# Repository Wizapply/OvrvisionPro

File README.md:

# OvrvisionPro
OvrvisionPro SDK - Open Source Project

## Licence
MIT License
Please read "LICENSE" file

# Folders
* 3rdparty : Third party files
* bin : Binaries
* board : PCB borad designs & parts list
* build : Project files for build
* docs : Resource for generating documents
* firmware : OvrvisionPro firmware sources&projects
* include : Public include files
* package
* samples The sample project for the SDK developing.
* src : Sources

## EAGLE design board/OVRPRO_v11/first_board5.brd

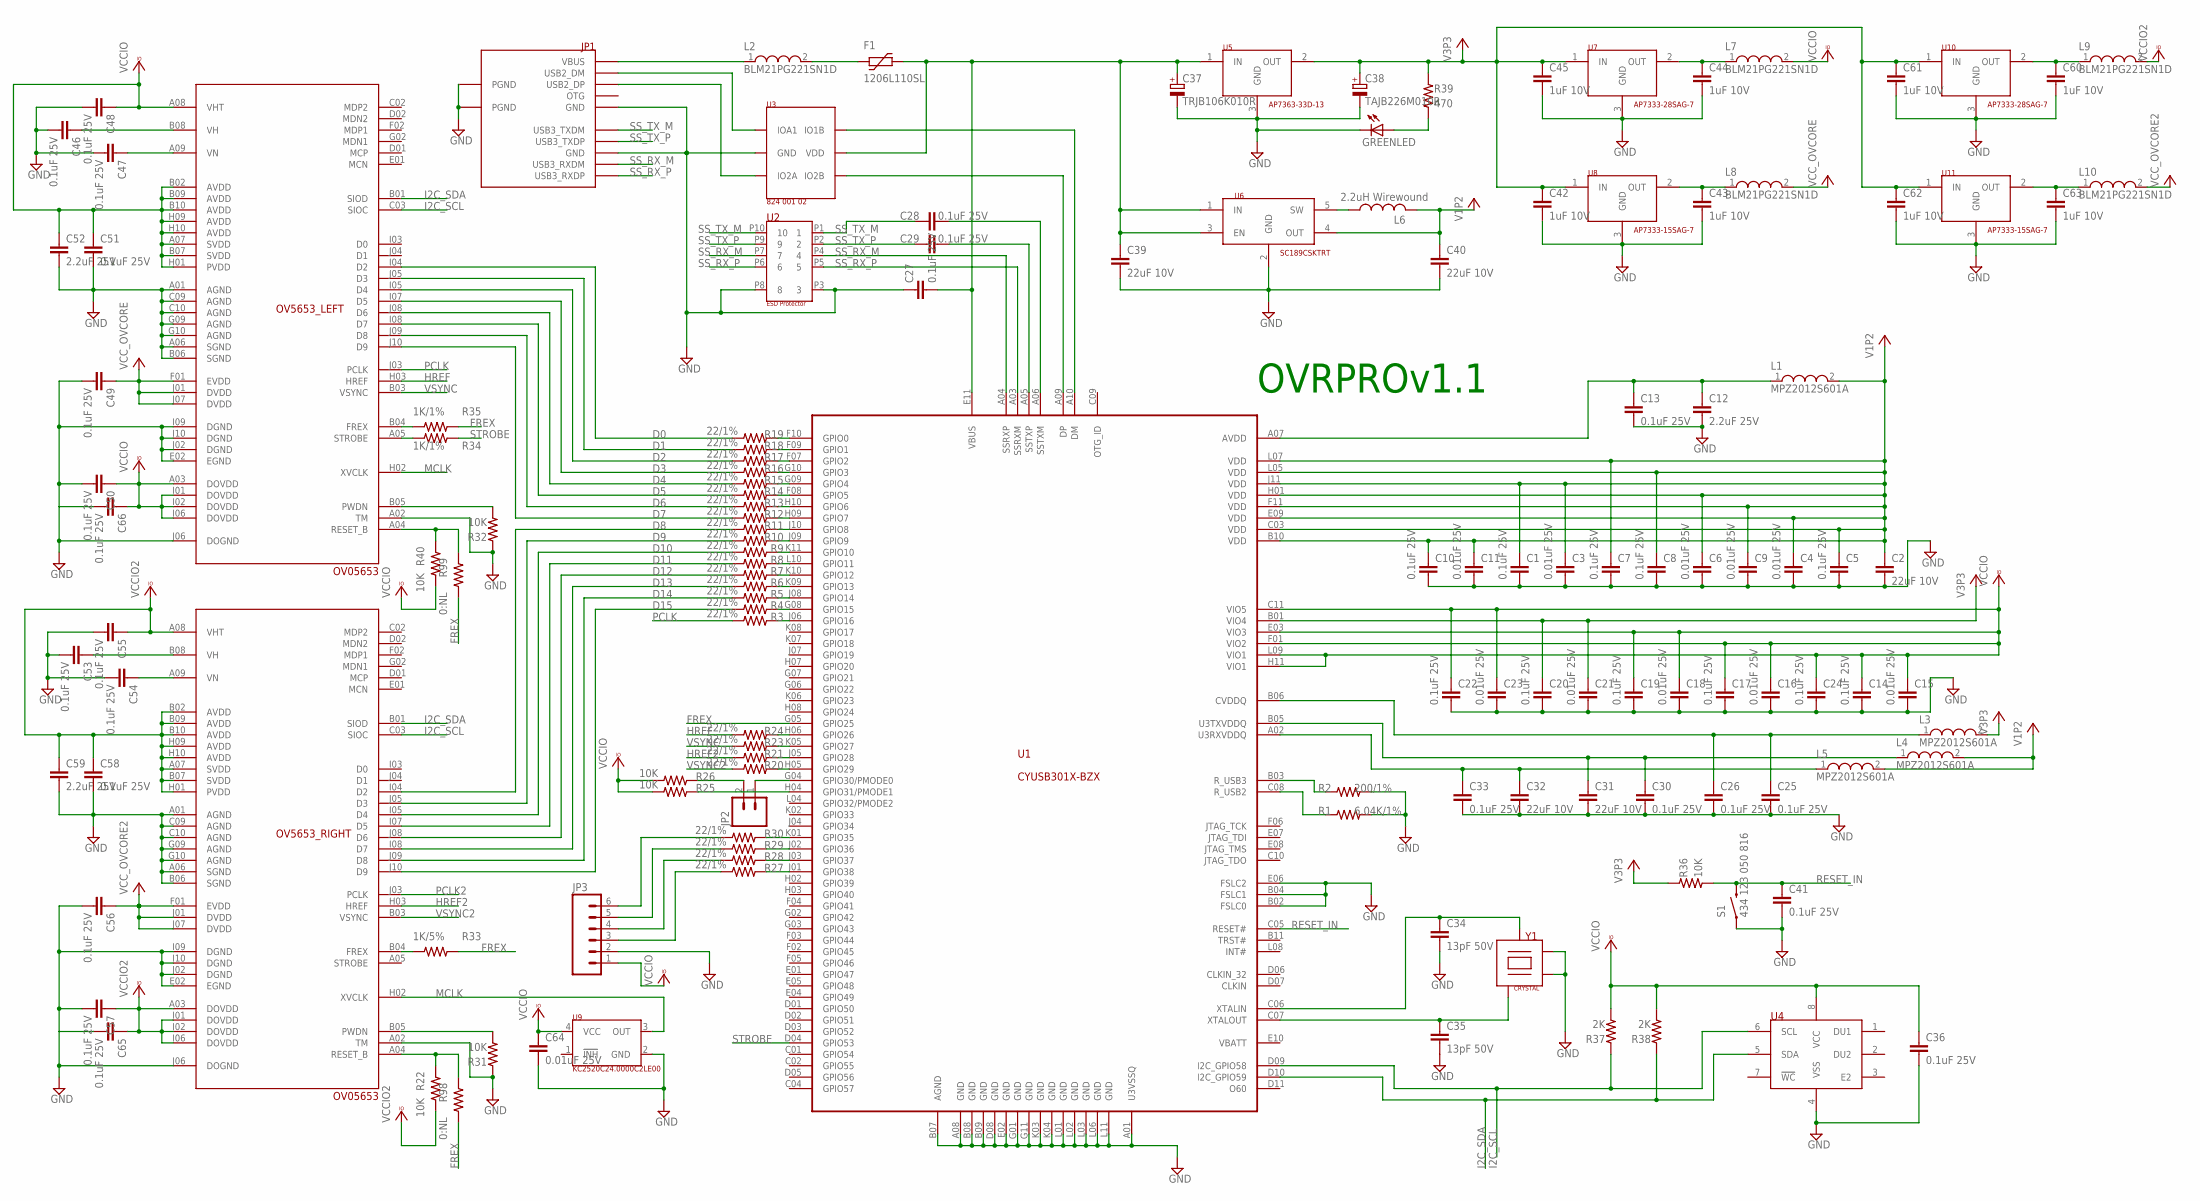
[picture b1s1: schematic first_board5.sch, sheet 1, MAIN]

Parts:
C1, C5, C7, C8, C10, C13, C14, C17, C19, C20, C22, C25, C26, C27, C28, C29, C30, C33, C46, C47, C48, C49, C50, C51, C53, C54, C55, C56, C57, C58, C65, C66: 0.1uF 25V; C0402K
C2, C31, C32, C39, C40: 22uF 10V; C1206
C3, C4, C6, C9, C11, C15, C16, C18, C21, C23, C64: 0.01uF 25V; C0402K
C12, C52, C59: 2.2uF 25V; C0805
C24, C36, C41: 0.1uF 25V; C0402
C34, C35: 13pF 50V; C0402K
C37: TRJB106K010R; CT3528
C38: TAJB226M010R; CT3528
C42, C43, C44, C45, C60, C61, C62, C63: 1uF 10V; C0402
F1: 1206L110SL; 1206L
GREENLED: LED_ESML0603; LED_SML0603
JP1: ZX360D-B-10PUSB3
JP2: M02PTH; 1X02
JP3: M06SILK_FEMALE_PTH; 1X06
L1, L3, L4, L5: MPZ2012S601A; WE-CBA_0805(W=3)
L2, L7, L8, L9, L10: BLM21PG221SN1D; WE-CBA_0805(W=3)
L6: 2.2uH Wirewound; L3225M
OV5653_LEFT, OV5653_RIGHT: OV05653-A66A
R1: 6.04K/1%; SMD1608
R2: 200/1%; SMD1608
R3, R4, R5, R6, R7, R8, R9, R10, R11, R12, R13, R14, R15, R16, R17, R18, R19, R20, R21, R23, R24, R27, R28, R29, R30: 22/1%; SMD1005
R22, R25, R26, R31, R32, R36, R40: 10K; SMD1608
R33: 1K/5%; SMD1005
R34, R35: 1K/1%; SMD1005
R37, R38: 2K; SMD1608
R39: 470; SMD1608
R98, R99: 0:NL; SMD1005
S1: 434 123 050 816; TACTILE-SWITCH-1101NE
U1: CYUSB301X-BZX; BGA121
U2: SP3010-04UTG
U3: WE-82400102
U4: M24M02-DRMN6TP; SO-08
U5: AP7363-33D-13; TO-252
U6: SC189CSKTRT; SOT23-5
U7, U10: AP7333-28SAG-7; SOT23
U8, U11: AP7333-15SAG-7; SOT23
U9: KC2520C24.0000C2LE00; KC2520C-C2
Y1: NX2520SACRY

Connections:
312: R15.2, U1.G09 (GPIO4)
321: R16.2, U1.G10 (GPIO3)
+3V3: C20.1, C21.1, C38.+, C42.1, C45.1, C61.1, C62.1, L3.2, R36.1, R39.1, U1.B01 (VIO4), U5.2 (OUT), U7.1 (IN), U8.1 (IN), U10.1 (IN), U11.1 (IN)
+5V: C1.1, C2.1, C3.1, C4.1, C5.1, C6.1, C7.1, C8.1, C9.1, C10.1, C11.1, C40.1, L1.2, L4.2, L5.2, L6.2, U1.B10 (VDD), U1.C03 (VDD), U1.E09 (VDD), U1.F11 (VDD), U1.H01 (VDD), U1.J11 (VDD), U1.L05 (VDD), U1.L07 (VDD), U6.4 (OUT)
D0: OV5653_LEFT.I04 (D2), R19.1
D1: OV5653_LEFT.J05 (D3), R18.1
D2: OV5653_LEFT.I05 (D4), R17.1
D3: OV5653_LEFT.I07 (D5), R16.1
D4: OV5653_LEFT.J08 (D6), R15.1
D5: OV5653_LEFT.I08 (D7), R14.1
D6: OV5653_LEFT.J09 (D8), R13.1
D7: OV5653_LEFT.J10 (D9), R12.1
D8: OV5653_RIGHT.I04 (D2), R11.1
D9: OV5653_RIGHT.J05 (D3), R10.1
D10: OV5653_RIGHT.I05 (D4), R9.1
D11: OV5653_RIGHT.I07 (D5), R8.1
D12: OV5653_RIGHT.J08 (D6), R7.1
D13: OV5653_RIGHT.I08 (D7), R6.1
D14: OV5653_RIGHT.J09 (D8), R5.1
D15: OV5653_RIGHT.J10 (D9), R4.1
FREX: R33.2, R35.2, R98.1, R99.1, U1.G05 (GPIO25)
GND: C1.2, C2.2, C3.2, C4.2, C5.2, C6.2, C7.2, C8.2, C9.2, C10.2, C11.2, C12.2, C13.2, C14.2, C15.2, C16.2, C17.2, C18.2, C19.2, C20.2, C21.2, C22.2, C23.2, C24.2, C25.2, C26.2, C27.1, C30.2, C31.2, C32.2, C33.2, C34.2, C35.2, C36.2, C37.-, C38.-, C39.2, C40.2, C41.2, C42.2, C43.2, C44.2, C45.2, C46.2, C47.2, C48.2, C49.2, C50.2, C51.2, C52.2, C53.2, C54.2, C55.2, C56.2, C57.2, C58.2, C59.2, C60.2, C61.2, C62.2, C63.2, C64.2, C65.2, C66.2, GREENLED.C, JP1.GND@1 (GND), JP1.GND@2 (GND), JP1.PGND@1 (PGND), JP1.PGND@2 (PGND), JP3.2, OV5653_LEFT.A01 (AGND), OV5653_LEFT.A02 (TM), OV5653_LEFT.A06 (SGND), OV5653_LEFT.B06 (SGND), OV5653_LEFT.C09 (AGND), OV5653_LEFT.C10 (AGND), OV5653_LEFT.E02 (EGND), OV5653_LEFT.G09 (AGND), OV5653_LEFT.G10 (AGND), OV5653_LEFT.I09 (DGND), OV5653_LEFT.I10 (DGND), OV5653_LEFT.J02 (DGND), OV5653_LEFT.J06 (DOGND), OV5653_RIGHT.A01 (AGND), OV5653_RIGHT.A02 (TM), OV5653_RIGHT.A06 (SGND), OV5653_RIGHT.B06 (SGND), OV5653_RIGHT.C09 (AGND), OV5653_RIGHT.C10 (AGND), OV5653_RIGHT.E02 (EGND), OV5653_RIGHT.G09 (AGND), OV5653_RIGHT.G10 (AGND), OV5653_RIGHT.I09 (DGND), OV5653_RIGHT.I10 (DGND), OV5653_RIGHT.J02 (DGND), OV5653_RIGHT.J06 (DOGND), R1.2, R2.2, R31.1, R32.1, S1.1, U1.A01 (U3VSSQ), U1.A08 (GND), U1.B02 (FSLC0), U1.B04 (FSLC1), U1.B07 (AGND), U1.B08 (GND), U1.B09 (GND), U1.D08 (GND), U1.E02 (GND), U1.E06 (FSLC2), U1.G01 (GND), U1.G11 (GND), U1.K03 (GND), U1.K04 (GND), U1.L01 (GND), U1.L02 (GND), U1.L03 (GND), U1.L06 (GND), U1.L11 (GND), U2.P3 (3), U2.P8 (8), U3.P2 (GND), U4.4 (VSS), U5.3 (GND), U6.2 (GND), U7.3 (GND), U8.3 (GND), U9.2 (GND), U10.3 (GND), U11.3 (GND), Y1.P2, Y1.P4
HREF: OV5653_LEFT.H03 (HREF), R24.1
HREF2: OV5653_RIGHT.H03 (HREF), R21.1
I2C_SCL: OV5653_LEFT.C03 (SIOC), OV5653_RIGHT.C03 (SIOC), R37.1, U1.D09 (I2C_GPIO58), U4.6 (SCL)
I2C_SDA: OV5653_LEFT.B01 (SIOD), OV5653_RIGHT.B01 (SIOD), R38.1, U1.D10 (I2C_GPIO59), U4.5 (SDA)
MCLK: OV5653_LEFT.H02 (XVCLK), OV5653_RIGHT.H02 (XVCLK), U9.3 (OUT)
unnamed: R2.1, U1.B03 (R_USB3)
unnamed: C12.1, C13.1, L1.1, U1.A07 (AVDD)
unnamed: R1.1, U1.C08 (R_USB2)
unnamed: JP2.2, R26.2
unnamed: R25.2, U1.H04 (GPIO31/PMODE1)
unnamed: C25.1, C26.1, L3.1, U1.B06 (CVDDQ)
unnamed: L6.1, U6.5 (SW)
unnamed: F1.P$1 (1), L2.2
unnamed: C44.1, L7.1, U7.2 (OUT)
unnamed: JP1.USB2_DM, U3.P1 (IOA1)
unnamed: JP1.USB2_DP, U3.P3 (IO2A)
unnamed: C32.1, C33.1, L5.1, U1.A02 (U3RXVDDQ)
unnamed: U1.A10 (DM), U3.P6 (IO1B)
unnamed: U1.A09 (DP), U3.P4 (IO2B)
unnamed: C30.1, C31.1, L4.1, U1.B05 (U3TXVDDQ)
unnamed: C34.1, U1.C06 (XTALIN), Y1.P1
unnamed: C35.1, U1.C07 (XTALOUT), Y1.P3
unnamed: GREENLED.A, R39.2
unnamed: C47.1, OV5653_LEFT.A09 (VN)
unnamed: C46.1, OV5653_LEFT.B08 (VH)
unnamed: C28.2, U1.A06 (SSTXM)
unnamed: C29.2, U1.A05 (SSTXP)
unnamed: OV5653_RIGHT.B05 (PWDN), R31.2
unnamed: JP3.6, R30.1
unnamed: OV5653_LEFT.B05 (PWDN), R32.2
unnamed: JP3.5, R29.1
unnamed: JP3.4, R28.1
unnamed: JP3.3, R27.1
unnamed: R30.2, U1.K01 (GPIO35)
unnamed: R29.2, U1.J02 (GPIO36)
unnamed: R28.2, U1.J03 (GPIO37)
unnamed: R27.2, U1.J01 (GPIO38)
unnamed: C27.2, C37.+, C39.1, F1.P$2 (2), U1.E11 (VBUS), U3.P5 (VDD), U5.1 (IN), U6.1 (IN), U6.3 (EN)
unnamed: JP1.VBUS, L2.1
unnamed: C43.1, L8.1, U8.2 (OUT)
unnamed: C60.1, L9.1, U10.2 (OUT)
unnamed: C63.1, L10.1, U11.2 (OUT)
unnamed: JP2.1, U1.G04 (GPIO30/PMODE0)
unnamed: OV5653_RIGHT.B04 (FREX), R33.1
unnamed: OV5653_LEFT.A05 (STROBE), R34.1
unnamed: R3.2, U1.J06 (GPIO16)
unnamed: R11.2, U1.J10 (GPIO8)
unnamed: R10.2, U1.J09 (GPIO9)
unnamed: R9.2, U1.K11 (GPIO10)
unnamed: R8.2, U1.L10 (GPIO11)
unnamed: R7.2, U1.K10 (GPIO12)
unnamed: R6.2, U1.K09 (GPIO13)
unnamed: R5.2, U1.J08 (GPIO14)
unnamed: R4.2, U1.G08 (GPIO15)
unnamed: R21.2, U1.J05 (GPIO28)
unnamed: R20.2, U1.H05 (GPIO29)
unnamed: OV5653_LEFT.B04 (FREX), R35.1
unnamed: R24.2, U1.H06 (GPIO26)
unnamed: R23.2, U1.K05 (GPIO27)
unnamed: R14.2, U1.F08 (GPIO5)
unnamed: R13.2, U1.H10 (GPIO6)
unnamed: R12.2, U1.H09 (GPIO7)
unnamed: R17.2, U1.F07 (GPIO2)
unnamed: R18.2, U1.F09 (GPIO1)
unnamed: R19.2, U1.F10 (GPIO0)
OV_RESET1: OV5653_LEFT.A04 (RESET_B), R40.2, R99.2
OV_RESET2: OV5653_RIGHT.A04 (RESET_B), R22.2, R98.2
PCLK: OV5653_LEFT.J03 (PCLK), R3.1
PCLK2: OV5653_RIGHT.J03 (PCLK)
RESET_IN: C41.1, R36.2, S1.2, U1.C05 (RESET#)
SS_RX_M: JP1.USB3_RXDM, U1.A04 (SSRXP), U2.P4 (4), U2.P7 (7)
SS_RX_P: JP1.USB3_RXDP, U1.A03 (SSRXM), U2.P5 (5), U2.P6 (6)
SS_TX_M: C28.1, JP1.USB3_TXDM, U2.P1 (1), U2.P10 (10)
SS_TX_P: C29.1, JP1.USB3_TXDP, U2.P2 (2), U2.P9 (9)
STROBE: R34.2, U1.D04 (GPIO53)
VCC: C49.1, L8.2, OV5653_LEFT.F01 (EVDD), OV5653_LEFT.J01 (DVDD), OV5653_LEFT.J07 (DVDD)
VCC2: C56.1, L10.2, OV5653_RIGHT.F01 (EVDD), OV5653_RIGHT.J01 (DVDD), OV5653_RIGHT.J07 (DVDD)
VCCIO: C14.1, C15.1, C16.1, C17.1, C18.1, C19.1, C22.1, C23.1, C24.1, C36.1, C48.1, C50.1, C51.1, C52.1, C55.1, C57.1, C58.1, C59.1, C64.1, C65.1, C66.1, JP3.1, L7.2, L9.2, OV5653_LEFT.A03 (DOVDD), OV5653_LEFT.A07 (SVDD), OV5653_LEFT.A08 (VHT), OV5653_LEFT.B02 (AVDD), OV5653_LEFT.B07 (SVDD), OV5653_LEFT.B09 (AVDD), OV5653_LEFT.B10 (AVDD), OV5653_LEFT.H01 (PVDD), OV5653_LEFT.H09 (AVDD), OV5653_LEFT.H10 (AVDD), OV5653_LEFT.I01 (DOVDD), OV5653_LEFT.I02 (DOVDD), OV5653_LEFT.I06 (DOVDD), OV5653_RIGHT.A03 (DOVDD), OV5653_RIGHT.A07 (SVDD), OV5653_RIGHT.A08 (VHT), OV5653_RIGHT.B02 (AVDD), OV5653_RIGHT.B07 (SVDD), OV5653_RIGHT.B09 (AVDD), OV5653_RIGHT.B10 (AVDD), OV5653_RIGHT.H01 (PVDD), OV5653_RIGHT.H09 (AVDD), OV5653_RIGHT.H10 (AVDD), OV5653_RIGHT.I01 (DOVDD), OV5653_RIGHT.I02 (DOVDD), OV5653_RIGHT.I06 (DOVDD), R22.1, R25.1, R26.1, R37.2, R38.2, R40.1, U1.C11 (VIO5), U1.E03 (VIO3), U1.F01 (VIO2), U1.H11 (VIO1), U1.L09 (VIO1), U4.8 (VCC), U9.4 (VCC)
VH: C53.1, OV5653_RIGHT.B08 (VH)
VN: C54.1, OV5653_RIGHT.A09 (VN)
VSYNC: OV5653_LEFT.B03 (VSYNC), R23.1
VSYNC2: OV5653_RIGHT.B03 (VSYNC), R20.1

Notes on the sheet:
OVRPROv1.1

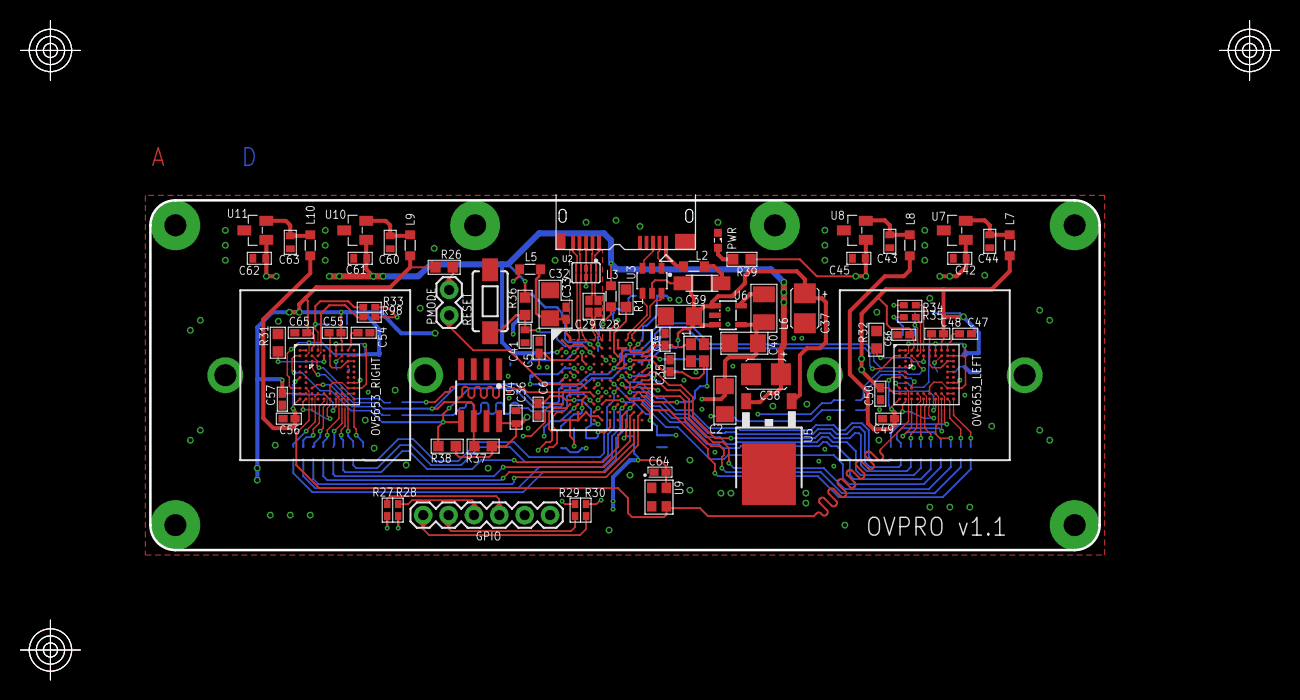
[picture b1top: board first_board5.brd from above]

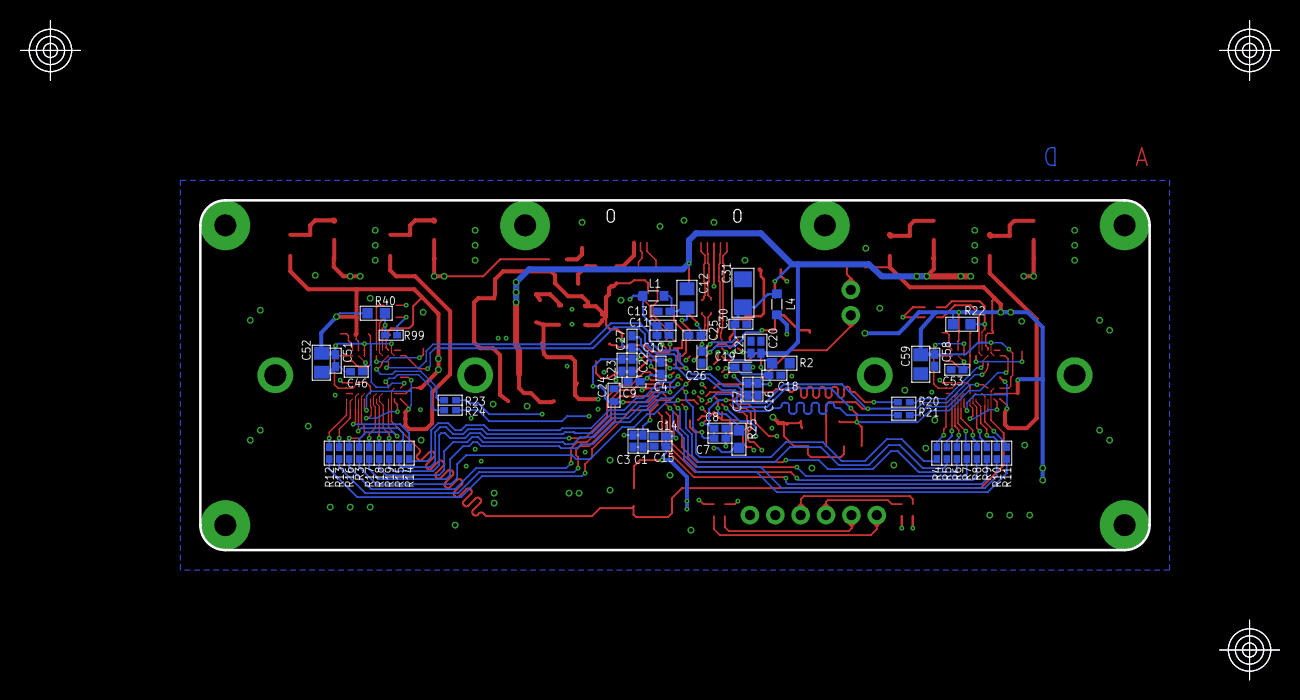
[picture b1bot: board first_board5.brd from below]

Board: 4 copper layers, 95.0 x 35.0 mm, 138 parts (60 on the bottom side), 103 nets.

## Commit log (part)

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2015-11-17 ヘッダファイルに埋め込んだカーネルからプログラムを生成
2015-11-17 add libraries
2015-11-18 ・ファームウェアを更新しました（EEPROMにセーブする機能） ・SDKにセーブ機能 ・C#プログラムにカメラ設定をリアルタイムに変更できるダイアログを追加 ・細かい関数の修正
2015-11-18 ・binフォルダ追加
2015-11-18 Modify create kernel
2015-11-18 RAWデータ（uchar）でデータを返すAPIも追加、Matを使いたくない場合はこちらも使用できます
2015-11-19 ・OvrvisionSDK for Unityを追加（AR部分は未実装） ・GetImageを一部変更
2015-11-19 samplesフォルダにサンプルコードを追加
2015-11-19 sampleのファイルを一部移動および削除
2015-11-19 サンプルプログラムにビルド後イベントを追加
2015-11-20 ・プロジェクトOpenCVの不具合を修正 ・OculusSDKv0.8をコミット ・oculus用のアプリケーションのプロジェクトを追加 ・::CoInitialize(NULL)関連の不具合を修正 ・UnityのARを追加（一部修正中）
2015-11-20 ・不具合を修正
2015-11-20 ・ovrvisionアプリケーションにOculusSDKのモノを追加
2015-11-21 OpenGL_windowsプロジェクトを追加
2015-11-21 sampleにモード切替追加。
2015-11-22 OpenGLサンプルプロジェクト追加
2015-11-22 フレームバッファをインスタンス生成で行う。 また、OpenGL/D3D連携のためのCPUへの転送を行わないAPIを追加
2015-11-23 OpenGL連携のテクスチャーAPI追加
2015-11-24 ・Ovrvision AR関連を追加しました。 ・Unityプログライン更新 ・キャリブレーションソフトウェアの不具合を修正しました。
2015-11-24 Direct3D連携の機能拡張チェック組み込み
2015-11-24 縮小グレースケール画像、スキンカラー抽出などのAPIを追加（未完成）
2015-11-25 GPUの拡張機能情報取得関数を追加。
2015-11-25 sample/OpenCVに画像保存を追加
2015-11-26 連携テクスチャー生成APIを追加
2015-11-26 手の色域調査
2015-11-27 ・トラッキング用のクラスを追加 ・Unity5プラグイン完成
2015-11-27 ・ARエンジン「Metaio」のプログラムを追加 ・OvrvisionProで起動が停止する不具合を修正 ・ファームウェアを更新
2015-11-27 ・アップロードできなかったので削除
2015-11-27 ・容量リミットのため削除
2015-11-27 画像取得時にクロップする関数を追加
2015-11-28 ・不具合の修正
2015-11-28 remove 1 project
2015-11-28 ・OvrvisionARを修正 ・Doxygen形式のコメントを追加
2015-11-28 色空間の検討
2015-11-29 片手の抽出。色相と彩度をハードコーディング
2015-11-30 両手の肌色抽出
2015-11-30 First Release
2015-11-30 ヒストグラム作成
2015-11-30 ガウシアンブラーで、疑似ピークをつぶす。照明の加減で色相が飛ぶことがあるが、これは今回は無視する
2015-12-01 ・ファームウェアを更新しました。
2015-12-01 ・公開するSDK修正
2015-12-01 複数GPUの場合、コア数と周波数の乗数が最も大きいものを選択する
2015-12-02 ・Version 1.01
2015-12-02 個々の画像から残存ノイズをerodeで削減。
2015-12-02 HSV色空間でmedianBlurをかけてノイズ除去後に色域抽出
2015-12-02 複数GPUの検出情報
2015-12-02 エピポーラ情報を読む
2015-12-02 左右のカメラのエピポーラ処理
2015-12-03 視差情報のテスト
2015-12-03 大きい域のみ考慮する
2015-12-03 ・簡易トラッキングを実装 ・Unity5での不具合を修正 ・一部カメラ起動が出来ない不具合を修正
2015-12-04 ・キャリブレーションツールの不具合を修正
2015-12-04 平行化修正案
2015-12-04 ステレオ平行化ほぼ修正
2015-12-04 ステレオ平行化修正版
2015-12-04 OpenCL関数の追加
2015-12-04 OpenCL動作テスト
2015-12-04 縮小の動作を確認
2015-12-05 HSV変換テスト
2015-12-05 縮小グレースケール関数を追加
2015-12-05 Remap修正しました
2015-12-05 色域判定関数を追加
2015-12-05 HSV変換の前にガウシアンブラーをかけた
2015-12-05 肌色領域マスク生成までOpenCLに実装
2015-12-06 追加gaussian blur
2015-12-06 ・Unityでの不具合を修正 ・高性能PCを動作させるとOvrvisionが停止する不具合を修正
2015-12-06 HSV色変換のバグ修正
2015-12-06 メディアンフィルターを実装、ガウシアンと比較評価中
2015-12-07 ・メモリリークの個所を確認 ・不具合を修正
2015-12-07 ・ドキュメントを更新
2015-12-07 リークテスト
2015-12-07 メモリリーク修正
2015-12-07 メディアンフィルターに5x5を追加して比較検討
2015-12-07 fix kernel
2015-12-08 ・一部メモリリークを修正
2015-12-08 肌色抽出用のカーネルを二種追加
2015-12-08 Close関数を追加。
2015-12-08 OpenGL連携テスト用のFreeGlutを追加
2015-12-09 ・カメラモードの切り替えを可能にしました。
2015-12-09 OpenGLテクスチャー連携テスト中
2015-12-09 OpenGL連携テストのためのコールバック関数追加
2015-12-09 コールバックプラットフォーム依存部分を切り分け
2015-12-09 GPUがOpenCL 1.2未満の場合、例外を投げて起動できないようにしました
2015-12-10 ・Version1.2
2015-12-10 ・OvrvisionProのカバーデザインをアップ
2015-12-10 肌色処理でOpenMPの効果を検討
2015-12-10 OpenMPで肌色領域テスト
2015-12-10 縮小画像の扱いを中断
2015-12-10 OpenMP化検討
2015-12-10 縮小画像を保持する準備
2015-12-10 縮小画像を残す
2015-12-10 暫定版の肌色抽出関数追加。まだ残存ノイズ多い
2015-12-10 合成カーネルの修正
2015-12-11 ・Unityのエラーを修正 ・CSharpのエラーを修正
2015-12-11 Remapかからないバグを修正
2015-12-11 肌色抽出処理のカーネルを修正
2015-12-11 肌色抽出でのGPU側リリースを修正
2015-12-11 Radeon 対応
2015-12-11 ・LensのDatasheepを追加 ・ドキュメントを更新
2015-12-12 ・ソースコードのエンコードをUTF-8Nに変更
2015-12-12 コメントなどを修正。機能的には変更なし
2015-12-12 ・Mac対応
2015-12-12 ・Mac用の画像USBストリームプログラムコードを追加
2015-12-12 MacOSに対応しました。 OpenCLの部分も一部変更しました。
2015-12-12 コード分析で指摘された部分の修正
2015-12-12 cl_eventの開放。
2015-12-12 OpenCLの開放漏れを修正
2015-12-12 肌色抽出の評価関数の閾値設定を追加
2015-12-13 凸包と凹状欠損で、手を絞り込む
2015-12-13 二段階で凸包の絞り込み。
2015-12-14 ・ホワイトバランス設定を修正
2015-12-14 ・ドキュメントの更新 ・ホワイトバランスオートの不具合を修正
2015-12-14 左右の画像の凸包をマッチング
2015-12-14 kalman filterによる抽出オブジェクトの追跡テスト
2015-12-14 肌色抽出の評価関数シミュレーション
2015-12-14 HSV変換のカーネル修正
2015-12-15 手の検出シミュレーション
2015-12-15 シミュレーションで100フレーム程度ヒストグラムをとって色範囲を特定。
2015-12-16 手の検出関数を追加、ただしまだ色範囲の推定が調整中で手が虫食い状態になる
2015-12-16 キャリブレーション結果を表示する
2015-12-16 手の抽出の縮小設定を追加
2015-12-16 五指の検出テスト（S）
2015-12-16 肌色推定を改良
2015-12-17 Charpの不具合を修正
2015-12-17 ・MacOSの開発
2015-12-17 ・MacOS開発
2015-12-17 check contour areas
2015-12-17 GPUとのテクスチャーシェアリングに伴う関数を追加。実装中
2015-12-17 GPUテクスチャーを実装、テスト中
2015-12-17 Sharing texture with OpenGL/D3D11
2015-12-18 ・MacOS
2015-12-18 MacOS開発と不具合調査
2015-12-19 GPUテクスチャー生成関数を追加。
2015-12-19 GPUテクスチャー関連関数の追加修正
2015-12-19 テクスチャー関係の整理
2015-12-19 GPUテクスチャーマージ
2015-12-19 テクスチャー関係関数を整理中
2015-12-19 MACOSXのスイッチも追加しましたが、問題あるかも
2015-12-20 MAXOSXでのOpenGL共有テクスチャーのコードが古かったので、一旦コメントアウト
2015-12-20 GPU共有テクスチャー修正
2015-12-20 MACOSX対応
2015-12-20 Xcode7では、これまで使用していたOpenCL/OpenGL共有テクスチャーの関数が使えなくなっているため、一旦ペンディング
2015-12-20 GPU共有テクスチャーの生成、更新関数を修正
2015-12-20 MACOSX対応の修正
2015-12-20 D3D11テスト用にDirectXTexライブラリを追加
2015-12-20 デバッグのため、GPU内の処理途中の画像を取得。テクスチャーが表示されない
2015-12-21 ・MACOSのコントロール
2015-12-21 ・ファームウェアテスト
2015-12-21 OpenGLの環境テスト中
2015-12-21 OpenCL1.2関数に絞って修正
2015-12-21 初期化バグ修正
2015-12-21 NVIDIA用のヘッダファイルを追加
2015-12-21 GPUテクスチャーのデータ取得
2015-12-21 OpenGLを指定した場合の異常系対処
2015-12-21 MACOSXではOpenGL連携関数が使えない？ので修正
2015-12-22 ・oculus sdk修正
2015-12-22 ・MACOSの
2015-12-22 ・MACOS キャリブレーションアプリ開発
2015-12-22 CheckGPUでOvrvisionPro適格性の判定を返す（メモリ容量については調査中）
2015-12-22 OpenCLバージョンも表示するよう追加
2015-12-22 暫定的にメモリ容量を判定
2015-12-23 ・ファームウェアでの検証と変更
2015-12-23 D3D11でのGPUテクスチャー動作テスト
2015-12-23 D3D11修正
2015-12-23 MACOSXではOpenGLの一部関数が有効になっていないため外す
2015-12-23 D3D11のGPU共有テクスチャー使用法をコメントに追加
2015-12-23 ヘッダファイルにGPU共有テクスチャーの使用法を追記
2015-12-24 ・ファーム調査
2015-12-24 コメント修正。機能的には変更なし
2015-12-24 MACOS
2015-12-24 ・Version1.4
2015-12-24 肌色抽出用カーネル追加
2015-12-24 肌色推定時のメッセージを変更
2015-12-25 肌色推定の精度改良にトーン補正用カーネル追加、
2015-12-26 諧調補正マップ追加
2015-12-26 縮小時の階調補正カーネル追加
2015-12-26 縮小時に階調補正かけて肌色推定の観察
2015-12-26 諧調補正マップ修正
2015-12-26 無駄コード削除
2015-12-27 肌色抽出のバグ修正
2015-12-27 OpenCLのイベントチェーンを修正
2015-12-27 Debugビルドができるように修正
2015-12-27 OpenGLテクスチャーのバグ修正
2015-12-28 ・制御部分修正
2015-12-28 OpenCLのイベントチェーン修正
2015-12-28 GPU共有テクスチャーのコメント追加
2015-12-28 MACOS v1.3
2015-12-28 OpenCLイベントチェーンを改良
2015-12-28 階調補正カーネルを追加
2015-12-29 ・Version 1.3
2015-12-29 Version 1.3 publish
2015-12-29 Version 1.3b mac publish
2015-12-30 ・ファームウェア変更
2015-12-30 OpenGLサンプルに肌色推定を組み込み
2015-12-31 テクスチャーの上下修正
2016-01-04 動作テスト用のプロジェクト修正
2016-01-04 動作テスト用OpenGLプロジェクト
2016-01-04 OpenGLプロジェクト修正
2016-01-05 レイテンシ測定。
2016-01-05 階調補正による肌色推定の精度改良
2016-01-05 GPU共有テクスチャーのレイテンシ測定
2016-01-06 ・ファームウェア改良 ・ハンドトラッキング改良
2016-01-07 D3D11のGPU共有テクスチャー修正
2016-01-07 MACOSX版にGPU共有テクスチャー組み込み
2016-01-07 MACOSX版とWindows版をマージ
2016-01-07 MACOSXコードをLinuxと分離
2016-01-07 MACOSXテクスチャー修正
2016-01-07 MACOSX版修正
2016-01-07 MACOSXでのGPU検出修正
2016-01-07 D3D11のGPU共有テクスチャーテストに肌色推定を追加
2016-01-08 ・Version 1.31
2016-01-08 ・バグ修正
2016-01-09 ・USB3.0の転送が停止する不具合を修正 ・USB3.0転送パフォーマンスを向上
2016-01-09 左右で異なるフィルター処理していたのを修正
2016-01-09 OpenCVプロジェクト外しました
2016-01-11 ・ovrvision_appの画像サイズを修正
2016-01-12 OpenCLのイベントチェーン強化
2016-01-12 肌色推定時のバグ修正
2016-01-12 Add TODO comment into UpdateImageTextures
2016-01-14 Version 1.32
2016-01-14 Version 1.32 firmware
2016-01-14 UpdateImageTexturesを修正、縮小画像もOpenGL共有テクスチャーとして使用できます
2016-01-14 OpenGLサンプルプロジェクト修正
2016-01-16 ・Version 1.4
2016-01-16 MAC Version 1.4
2016-01-21 Modify for linux edition
2016-01-22 Prepare for Linux edition
2016-01-22 Prototype of Linux edition
2016-01-22 カメラ制御以外をLinux用に修正。カメラ部分は未実装
2016-01-22 Linux edition UNDER CONDTRUCTION
2016-01-23 Video4Linuxのフォーマット指定を変更
2016-01-23 Fix V4l functions
2016-01-23 Add QueryCapability to Video4Linux
2016-01-25 Add Video4Linux query program
2016-01-28 V4Lの接続テスト
2016-01-28 ・Unityの使いやすさ向上
2016-01-28 V4Lカメラ情報取得
2016-01-28 Modify V4L
2016-01-28 Search 'OvrvisionPro' device
2016-01-29 ・UnityのOpenGL不具合修正
2016-01-29 Modify MMAP mode on V4L
2016-01-29 Set resolution on V4L
2016-01-30 V4L capture test
2016-02-01 ・プロジェクト移動 ・ARのシステムを最適化 ・ファームウェア修正
2016-02-02 Version 1.5
2016-02-02 ・Version 1.5 docs
2016-02-03 Fix crop image on V4L2
2016-02-04 ・FirmGPIOテスト ・UnityでDirectX12を実装、開発中
2016-02-05 V4L camera control NOT YET IMPLEMENTED
2016-02-06 ・RAW描画を追加
2016-02-06 mac os
2016-02-06 ・registerを削除 ・
2016-02-06 Add crop to V4L2
2016-02-08 Linux対応(途中)
2016-02-09 ・Ｌｉｎｕｘ対応（開発中）
2016-02-09 ・Linux対応(開発中)
2016-02-09 ・セカンドロット用のリスト変更
2016-02-09 Add linux eclipse project
2016-02-09 Add Jetson TK1 project
2016-02-10 Modify Jetson TK1 sample
2016-02-10 JetsonTK1用のCUDA代替コード追加
2016-02-10 Add CUDA project for Jetson TK1
2016-02-10 Modify CUDA project
2016-02-11 CUDAファイル修正
2016-02-11 OpenCVバージョン切り替え
2016-02-11 modify main.cpp
2016-02-12 Modify CUDA project for Jetson TK1
2016-02-12 Modyfy project
2016-02-13 ・Linux対応(公開に向けての準備)
2016-02-13 Modify main.cpp of CUDA version
2016-02-15 ・Linux x86_64 バージョン
2016-02-15 ・Version 1.6
2016-02-15 Jetson TK1での処理実験
2016-02-17 Jetson TK1 ZEROCOPY実験
2016-02-17 Modify Jetson CUDA code
2016-02-17 Jetson ZEROCOPY Demosaicing
2016-02-17 Check CudaMem step
2016-02-17 V4L関数追加
2016-02-17 Fix V4L new function
2016-02-29 Unity更新
2016-03-05 ・Version1.7
2016-03-08 ・マニュアルにマーカージェネレータ追加
2016-03-08 MAC v1.7
2016-03-11 不具合を修正。プロジェクトを整理
2016-03-12 Remove ovrvisionlinux.*
2016-03-19 ・オープンソースプロジェクト
2016-03-19 ・Unity Plugin x86不具合修正
2016-03-22 ・Unityの不具合を修正
2016-03-29 OpenSoruce project
2016-04-06 Firmware 1.2
2016-04-06 Firmware 1.3
2016-04-09 ・Oculus app bug fixed
2016-04-19 ・Firmware bug fixed
2016-05-14 ・Firmware Update
2016-05-19 Add Callback Functions for windows
2016-05-19 Add Callback Functions for machos
2016-05-19 Add Callback Functions for V4L
2016-05-20 Support Oculus SDK1.3.2
2016-05-31 Version 1.7
2016-05-31 Version 1.7 unity
2016-06-13 linux callback 修正
2016-06-13 Add CMakeLists.txt for linux
2016-06-13 Add GLUT sample
2016-06-13 OpenGL on linux動作チェック
2016-06-14 Update OpenGL sample
2016-06-14 Modify OpenGL sample for linux
2016-06-18 Add source and project files
2016-06-18 Code added
2016-06-18 Modify Debug project of CUDA
2016-06-19 Remove link of unused libs
2016-06-19 CUDA修正
2016-06-19 CUDAではCV_8UC3でデータを取得
2016-06-20 Update CUDA project for Linux
2016-06-20 Update CUDA project
2016-06-21 Show right image
2016-06-21 use imshow(GpuMat)
2016-06-22 Modify for Linux
2016-06-22 Modify Makefile
2016-06-23 Fix Makefile
2016-06-23 Remove unused folder
2016-06-23 Add CMakeLists.txt
2016-06-27 OpenCVにWITH_GPUおよびOpenGLを追加
2016-07-03 フィルター選択のマクロ修正
2016-07-08 ・Update firmware
2016-07-09 update firmware
2016-09-02 support Oculus SDK v1.7
2016-09-04 oculus1.7
2016-09-29 ENH: Enabled option to allow client to choose OpenCL vendor implementation
2016-10-12 ・Oculus SDK v1.8 support
2016-10-12 docs update
2016-10-14 new CV1, HTC Vive Mounter
2016-10-16 Add Intel Media Accelerator project
2016-10-27 update datasheet
2016-11-03 firmware bug fixed
2016-11-03 firmware update
2016-12-21 support libSGM
2016-12-29 add libsgm
2017-02-15 libsgmを更新
2017-03-01 remove old opencv
2017-03-01 Add new version opencv
2017-03-01 rename vs2013_new to vs2015
2017-03-01 fix ovrvision.dll build for vs2015
2017-03-01 Add windows build
2017-03-01 Add x64 build
2017-11-17 Calibration Bug Fixed
2017-11-18 calibration Update
2017-12-06 update libsgm
2018-01-17 opencl update
2018-01-19 calibraion error fixed
2018-01-19 version 1.90
2018-09-20 Add processing of USB startup error
2019-07-01 1. Build support for Visual Stduio 2019. 2. Fixed GPU(opencl) selection issues. 3. Fixed bugs in the OpenCL program.
2019-07-06 Update Xcode project (MACOS)
2019-12-26 Add JetsonNano
2019-12-26 Add cu files
2020-01-21 Add Visual Studio 2019
2020-01-22 Modify
2020-01-23 Modify for 4.1.2
2020-01-24 OpenCV-4.1.2
2020-01-24 不要なコードを削除
2020-01-25 Modify solution
2020-01-27 OpenCV_4.1.2.props追加
2020-01-27 パス修正
2020-01-27 Debugモード修正
2020-03-10 Added support for VisualStudio2019.
2020-03-10 Added support for VisualStduio2019
2020-10-03 Merged with Wizapply on 2020 Oct 4
2021-05-06 Update OpenCL and project files
2021-11-06 Fix lib folder
2021-11-06 Add symbolic link to Video4Linux
2021-11-10 Add Test project for See in the Dark

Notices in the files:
board/OVRPRO_v11/first_board5.brd:
Copyright(C)2015 Wizapply.
parts and their libraries:
SparkFun-Connectors: Licensing: Creative Commons ShareAlike 4.0 International - https://creativecommons.org/licenses/by-sa/4.0
EMCComponents: Copyright: Wurth Elektronik
EMCComponents: Copyright: Würth Elektronik
